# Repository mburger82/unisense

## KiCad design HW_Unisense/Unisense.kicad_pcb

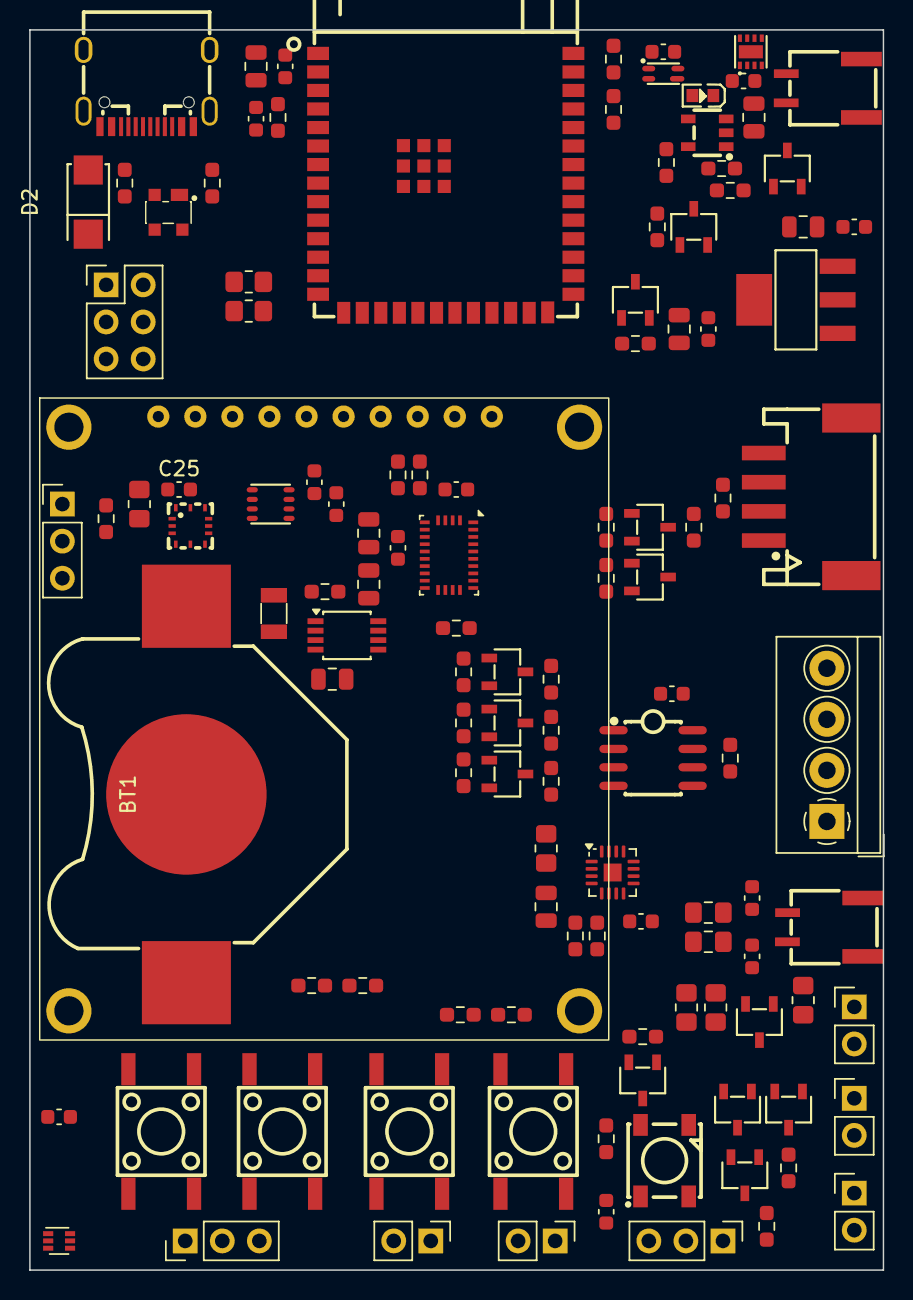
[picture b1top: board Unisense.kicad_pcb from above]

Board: 2 copper layers, 58.5 x 85.0 mm, 121 parts (1 on the bottom side), 74 nets, no tracks yet.

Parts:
BT1: Battery_Cell; BAT-SMD_MYOUNG_MY-2032-04
C1, C2, C5, C6, C8, C9, C10, C11, C12, C13, C14, C16, C17, C22, C25: 100n; C_0603_1608Metric
C3, C4, C7, C15, C21: 10u; C_0805_2012Metric
C18: 1uF; C_0805_2012Metric
C19, C20: 100nF; C_0805_2012Metric
C23, C24: 220pF; C_0603_1608Metric
D1: PRTR5V0U2X_C2827688; SOT-143-4_L2.9-W1.3-P1.92-LS2.4-BL
D2: SS24K; SMA_L4.3-W2.6-LS5.1-R-RD
FB1, FB2: FerriteBead; L_0805_2012Metric_Pad1.15x1.40mm_HandSolder
J1: Conn_02x03_Odd_Even; PinHeader_2x03_P2.54mm_Vertical
J2: SW1; PinHeader_1x02_P2.54mm_Vertical
J3: SW2; PinHeader_1x02_P2.54mm_Vertical
J4: GeigerCounter; PinHeader_1x03_P2.54mm_Vertical
J5: WS2812; PinHeader_1x03_P2.54mm_Vertical
J6: LED1; PinHeader_1x02_P2.54mm_Vertical
J7: LED2; PinHeader_1x02_P2.54mm_Vertical
J8: LED3; PinHeader_1x02_P2.54mm_Vertical
J9: RS485; TerminalBlock_4Ucon_1x04_P3.50mm_Horizontal
J10: OneWire; PinHeader_1x03_P2.54mm_Vertical
JP1: SolderJumper_3_Open; SolderJumper-3_P1.3mm_Open_Pad1.0x1.5mm
LED1: WS2812B-B/W; LED-SMD_4P-L5.0-W5.0-TL_WS2812B-B
LED2: 19-217/BHC-ZL1M2RY/3T; LED0603-FD_BLUE
P1, P2: SM02B-NSHSS-TB(LF)(SN); CONN-SMD_SM02B-NSHSS-TB-LF-SN
Q1, Q2, Q3, Q4, Q11, Q12, Q13: BSN20; SOT-23-3_L2.9-W1.6-P1.90-LS2.8-BR
Q5, Q6, Q7: AO3400A; SOT-23-3_L2.9-W1.6-P1.90-LS2.8-BR
Q8, Q9, Q10: IRLML6402TRPBF; SOT-23-3_L2.9-W1.6-P1.90-LS2.8-BR
R1, R2, R43: 0R; R_0805_2012Metric_Pad1.20x1.40mm_HandSolder
R3, R4, R20, R21: 5.1k; R_0603_1608Metric_Pad0.98x0.95mm_HandSolder
R5, R12, R16, R22, R23, R24, R25, R41, R42: 100k; R_0603_1608Metric_Pad0.98x0.95mm_HandSolder
R6, R7, R8, R9, R10, R11, R13, R14, R26, R27, R28, R29, R30, R31, R36: 1k; R_0603_1608Metric_Pad0.98x0.95mm_HandSolder
R15: 21k; R_0603_1608Metric_Pad0.98x0.95mm_HandSolder
R17, R18, R19: 75R; R_0805_2012Metric_Pad1.20x1.40mm_HandSolder
R32, R33, R34, R37, R39, R40: 10k; R_0603_1608Metric_Pad0.98x0.95mm_HandSolder
R35: 33k; R_0603_1608Metric_Pad0.98x0.95mm_HandSolder
R38: 4R7; R_0805_2012Metric_Pad1.20x1.40mm_HandSolder
SW1, SW2, SW3, SW4: K2-1102SP-C4SC-04; KEY-SMD_4P-L6.0-W6.0-P4.50-LS9.5-BL
U1: ESP32-S3-WROOM-1(N8R2); WIRELM-SMD_ESP32-S3-WROOM-1
U2: S4B-PH-SM4-K-TB(LF)(SN); CONN-SMD_S4B-PH-SM4-K-TB-LF-SN
U3: LD1117S33TR; SOT-223_L6.5-W3.5-P2.30-LS7.0-BR
U4: TMP112xxDRL; SOT-563
U5: BME280; LGA-8_BME280_BL
U6: BNO055; LGA-28_5.2x3.8mm_P0.5mm
U7: VEML6040A3OG; SENSOR_SMD_VEML6040A3OG
U8: MCP73831T-2ATI/OT; SOT-23-5_L3.0-W1.7-P0.95-LS2.8-BR
U9: MAX17048G+T10; DFN-8_L2.0-W2.0-P0.50-BL-EP
U10: SP3485EN-L/TR; SOIC-8_L5.0-W4.0-P1.27-LS6.0-BL
U11: PCF85263ATT; TSSOP-8_3x3mm_P0.65mm
U12: MAX98357A; TQFN-16-1EP_3x3mm_P0.5mm_EP1.23x1.23mm
U13: ZMOD4510AI1R; LGA-12_L3.0-W3.0-P0.50-BL_ZMOD4410AI1V
USBC1: USB3.1C16PFSMT; USB-C-SMD_TYPE-C-USB-17
X1: DFR0649
Y1: Crystal; Crystal_SMD_3215-2Pin_3.2x1.5mm

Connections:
+3.3V: C2.1, C3.1, C6.1, C7.1, J1.2, Q10.2 (S), R5.2, R12.1, R16.1, R23.2, R24.2, U1.2 (3V3), U3.2 (VOUT), U3.4 (VOUT)
+3.3V_SW: C9.1, C10.1, C12.1, C13.1, C14.2, C18.1, C19.1, C21.1, C22.1, C25.2, J10.1, JP1.1 (A), Q1.1 (G), Q2.1 (G), Q3.1 (G), Q4.1 (G), Q10.3 (D), Q11.1 (G), Q12.1 (G), Q13.1 (G), R6.2, R7.2, R10.2, R13.2, R26.2, R28.2, R30.2, R36.2, R38.2, R42.1, U4.5 (V+), U5.2 (CSB), U5.6 (VDDIO), U5.8 (VDD), U6.3 (VDD), U6.4 (~BOOT_LOAD_PIN), U6.28 (VDDIO), U7.4 (VDD), U11.8 (VDD), U12.7 (VDD), U12.8 (VDD), U13.5 (VDD), U13.11 (RES_N), U13.12 (VDDIO)
+3V3: R33.1, R34.1
+5V: C4.1, C5.1, D2.2 (K), Q8.2 (S), Q9.2 (S), U3.3 (VIN)
+5V_SW: C8.1, C17.1, J4.2, J5.1, J9.4, JP1.3 (B), LED1.1 (VDD), Q9.3 (D), R11.2, R14.2, R17.2, R18.2, R19.2, R27.2, R29.2, R31.2, U10.8 (VCC), X1.1 (VCC)
+BATT: C15.1, C16.1, P1.1, Q8.3 (D), U8.3 (VBAT), U9.2 (CELL), U9.3 (VDD)
/USB_D+: R2.2, U1.14 (IO20)
/USB_D-: R1.2, U1.13 (IO19)
D+: D1.2, R2.1, USBC1.A6 (DP1), USBC1.B6 (DP2)
D-: D1.3, R1.1, USBC1.A7 (DN1), USBC1.B7 (DN2)
EN: C1.1, J1.1, R5.1, SW1.3, SW1.4, U1.3 (EN)
ESP_RXD: J1.5, U1.36 (RXD0)
ESP_TXD: J1.3, U1.37 (TXD0)
EnPower: Q9.1 (G), Q10.1 (G), R23.1, R24.1, U1.32 (IO39)
GC_Data: R15.1, R35.2, U1.33 (IO40)
GND: BT1.2 (-), C1.2, C2.2, C3.2, C4.2, C5.2, C6.2, C7.2, C8.2, C9.2, C10.2, C11.2, C12.2, C13.2, C14.1, C15.2, C16.2, C17.2, C18.2, C19.2, C20.2, C21.2, C22.2, C23.2, C24.2, C25.1, D1.1, J1.4, J2.2, J3.2, J4.3, J5.3, J9.3, J10.3, LED1.3 (VSS), P1.2, P1.3, P1.4, P2.3, P2.4, Q5.2 (S), Q6.2 (S), Q7.2 (S), R3.1, R4.1, R21.2, R22.1, R35.1, R37.2, R39.2, R40.2, R41.2, R43.2, SW1.1, SW1.2, SW2.1, SW2.2, SW3.1, SW3.2, SW4.1, SW4.2, U1.1 (GND), U1.40 (GND), U1.41 (GND), U2.4, U2.5, U2.6, U3.1 (GND), U4.2 (GND), U4.4 (ADD0), U5.1 (GND), U5.5 (SDO), U5.7 (GND), U6.2 (GND), U6.10 (BL_IND), U6.15 (GNDIO), U6.16 (GNDIO), U6.18 (COM2), U6.25 (GNDIO), U7.1 (GND), U8.2 (VSS), U9.1 (CTG), U9.4 (GND), U9.6 (QSTRT), U9.9 (EP), U10.5 (GND), U11.4 (VSS), U12.3 (GND), U12.11 (GND), U12.15 (GND), U12.17 (PAD), U13.6 (VSS), U13.7 (VSS), U13.9 (VSS), USBC1.0, USBC1.A1 (GND), USBC1.A12 (GND), X1.2 (GND)
IO0: J1.6, SW2.3, SW2.4, U1.27 (IO0)
LED1: Q5.1 (G), U1.16 (IO46)
LED2: Q6.1 (G), U1.17 (IO9)
LED3: Q7.1 (G), U1.18 (IO10)
LS+: C24.1, FB1.2, P2.1
LS-: C23.1, FB2.2, P2.2
unnamed: BT1.1 (+), C20.1, U11.3 (VBAT)
unnamed: J4.1, R15.2
unnamed: J5.2, Q4.3 (D), R14.1
unnamed: J6.1, R17.1
unnamed: J6.2, Q5.3 (D)
unnamed: J7.1, R18.1
unnamed: J7.2, Q6.3 (D)
unnamed: J8.1, R19.1
unnamed: J8.2, Q7.3 (D)
unnamed: JP1.2 (C), R8.2, R9.2, U2.3
unnamed: LED1.4 (DIN), Q3.3 (D), R11.1
unnamed: LED2.1 (C), R20.1
unnamed: Q1.3 (D), R8.1, U2.1
unnamed: Q2.3 (D), R9.1, U2.2
unnamed: R32.2, Y1.1
unnamed: C11.1, U6.9 (CAP)
unnamed: R40.1, U6.17 (COM3)
unnamed: R39.1, U6.6 (PS0)
unnamed: R37.1, U6.5 (PS1)
unnamed: R21.1, U8.5 (PROG)
unnamed: R20.2, U8.1 (STAT)
unnamed: R32.1, U11.1 (OSCI)
unnamed: U11.2 (OSCO), Y1.2
unnamed: R43.1, U12.2 (GAIN_SLOT)
unnamed: FB2.1, U12.10 (OUTN)
unnamed: FB1.1, U12.9 (OUTP)
unnamed: R41.1, R42.2, U12.4 (~SD_MODE)
unnamed: R38.1, U13.10 (VDDH)
unnamed: R4.2, USBC1.A5 (CC1)
unnamed: R3.2, USBC1.B5 (CC2)
OnWire_Data: J10.2, R36.1, U1.31 (IO38)
RS485_A: J9.1, R25.1, U10.6 (A)
RS485_B: J9.2, R25.2, U10.7 (B)
RS485_EN: Q12.2 (S), R28.1, U1.6 (IO6)
RS485_EN_5V: Q12.3 (D), R29.1, U10.2 (RE#), U10.3 (DE)
RS485_RX: Q13.2 (S), R30.1, U1.11 (IO18)
RS485_RX_5V: Q13.3 (D), R31.1, U10.1 (RO)
RS485_TX: Q11.2 (S), R26.1, U1.10 (IO17)
RS485_TX_5V: Q11.3 (D), R27.1, U10.4 (DI)
SCL: Q1.2 (S), R6.1, R33.2, U1.39 (IO1), U4.1 (SCL), U5.4 (SCK), U6.19 (COM1), U7.3 (SCL), U9.7 (SCL), U11.6 (SCL), U13.1 (SCL)
SDA: Q2.2 (S), R7.1, R34.2, U1.38 (IO2), U4.6 (SDA), U5.3 (SDI), U6.20 (COM0), U7.2 (SDA), U9.8 (SDA), U11.5 (SDA), U13.2 (SDA)
SPI0_CLK: U1.22 (IO14), X1.3 (SCLK)
SPI0_MISO: U1.20 (IO12), X1.5 (MISO)
SPI0_MOSI: U1.21 (IO13), X1.4 (MOSI)
SW1: J2.1, R12.2, SW3.3, SW3.4, U1.35 (IO42)
SW2: J3.1, R16.2, SW4.3, SW4.4, U1.34 (IO41)
TFT_CS: U1.19 (IO11), X1.6 (CS)
TFT_DC: U1.9 (IO16), X1.8 (DC)
V_USB: D1.4, D2.1 (A), LED2.2 (A), Q8.1 (G), R22.2, U8.4 (VDD), USBC1.A4 (VBUS), USBC1.A9 (VBUS)
WS2812_Data1: Q3.2 (S), R10.1, U1.7 (IO7)
WS2812_Data2: Q4.2 (S), R13.1, U1.8 (IO15)
~General_Reset: U1.12 (IO8), X1.7 (RES)

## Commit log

2023-06-27 rename folder
2023-07-03 add power switching. Add Battery management
2023-08-16 add more sensors and arrange on multiple pages
2024-04-08 change power net names, as V8 handles them like a champ
2024-04-26 add mor sensors, place parts
